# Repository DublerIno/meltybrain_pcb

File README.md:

first iteration of our pcb for melty brain

we are using esp32s3 supermini and high g H3LIS331DL accelerometr. 

to fix:
- vias should not be under the h3 package
- maybe change mounting holes for less mechanical stress of board

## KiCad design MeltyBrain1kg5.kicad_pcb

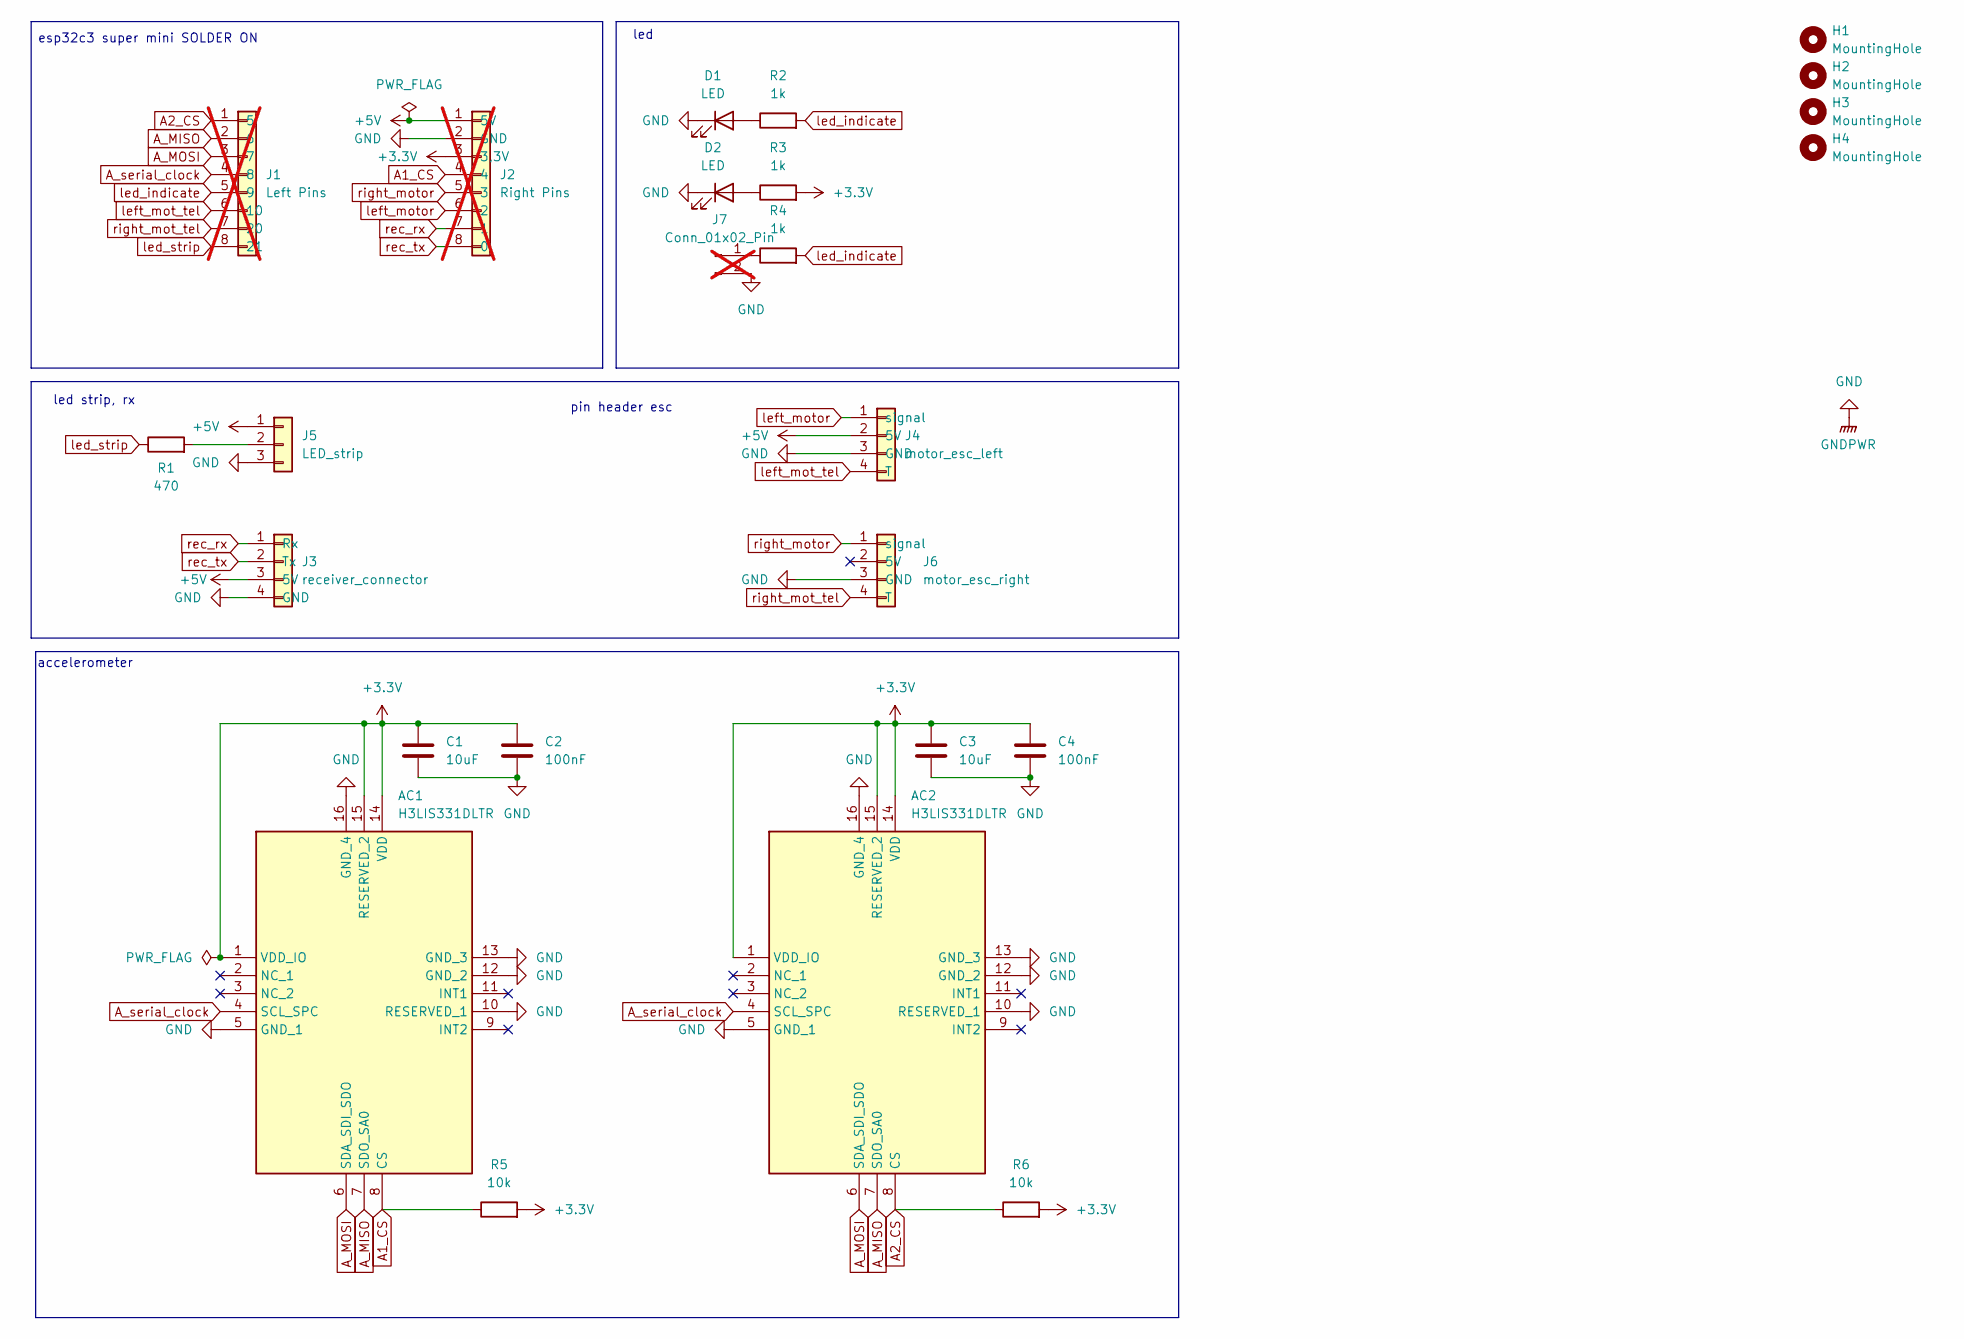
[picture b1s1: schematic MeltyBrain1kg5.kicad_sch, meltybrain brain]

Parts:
AC1, AC2: H3LIS331DLTR; LIS3DHTR; Manufacturer_Part_Number H3LIS331DLTR; Mouser Part Number 511-H3LIS331DLTR
C1, C3: 10uF; C_0603_1608Metric_Pad1.08x0.95mm_HandSolder
C2, C4: 100nF; C_0603_1608Metric_Pad1.08x0.95mm_HandSolder
D1, D2: LED; D_0603_1608Metric_Pad1.05x0.95mm_HandSolder
H1, H2, H3, H4: MountingHole; MountingHole_2.2mm_M2
J1: Left Pins; PinHeader_1x08_P2.54mm_Vertical; not fitted
J2: Right Pins; PinHeader_1x08_P2.54mm_Vertical; not fitted
J3: receiver_connector; JST_SH_BM04B-SRSS-TB_04x1.00mm_Straight
J4: motor_esc_left; PinHeader_1x04_P2.54mm_Vertical
J5: LED_strip; PinHeader_1x03_P2.54mm_Vertical
J6: motor_esc_right; PinHeader_1x04_P2.54mm_Vertical
J7: Conn_01x02_Pin; PinSocket_1x02_P2.54mm_Vertical; not fitted
R1: 470; R_0603_1608Metric_Pad0.98x0.95mm_HandSolder
R2, R3, R4: 1k; R_0603_1608Metric_Pad0.98x0.95mm_HandSolder
R5, R6: 10k; R_0603_1608Metric_Pad0.98x0.95mm_HandSolder

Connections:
+3.3V: AC1.1 (VDD_IO), AC1.14 (VDD), AC1.15 (RESERVED_2), AC2.1 (VDD_IO), AC2.14 (VDD), AC2.15 (RESERVED_2), C1.1, C2.1, C3.1, C4.1, J2.3 (3,3V), R3.2, R5.2, R6.2
+5V: J2.1 (5V), J3.3 (5V), J4.2 (5V), J5.1
A1_CS: AC1.8 (CS), J2.4, R5.1
A2_CS: AC2.8 (CS), J1.1 (5), R6.1
A_MISO: AC1.7 (SDO_SA0), AC2.7 (SDO_SA0), J1.2 (6)
A_MOSI: AC1.6 (SDA_SDI_SDO), AC2.6 (SDA_SDI_SDO), J1.3 (7)
A_serial_clock: AC1.4 (SCL_SPC), AC2.4 (SCL_SPC), J1.4 (8)
GND: AC1.5 (GND_1), AC1.10 (RESERVED_1), AC1.12 (GND_2), AC1.13 (GND_3), AC1.16 (GND_4), AC2.5 (GND_1), AC2.10 (RESERVED_1), AC2.12 (GND_2), AC2.13 (GND_3), AC2.16 (GND_4), C1.2, C2.2, C3.2, C4.2, D1.1 (K), D2.1 (K), J2.2 (GND), J3.4 (GND), J4.3 (GND), J5.3, J6.3 (GND), J7.2
unnamed: D1.2 (A), R2.1
unnamed: D2.2 (A), R3.1
unnamed: J5.2, R1.2
unnamed: J7.1, R4.1
led_indicate: J1.5 (9), R2.2, R4.2
led_strip: J1.8 (21), R1.1
left_mot_tel: J1.6 (10), J4.4 (T)
left_motor: J2.6 (2), J4.1 (signal)
rec_rx: J2.7 (1), J3.1 (Rx)
rec_tx: J2.8 (0), J3.2 (Tx)
right_mot_tel: J1.7 (20), J6.4 (T)
right_motor: J2.5 (3), J6.1 (signal)

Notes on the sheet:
led strip, rx
accelerometer
pin header esc
esp32c3 super mini SOLDER ON
led

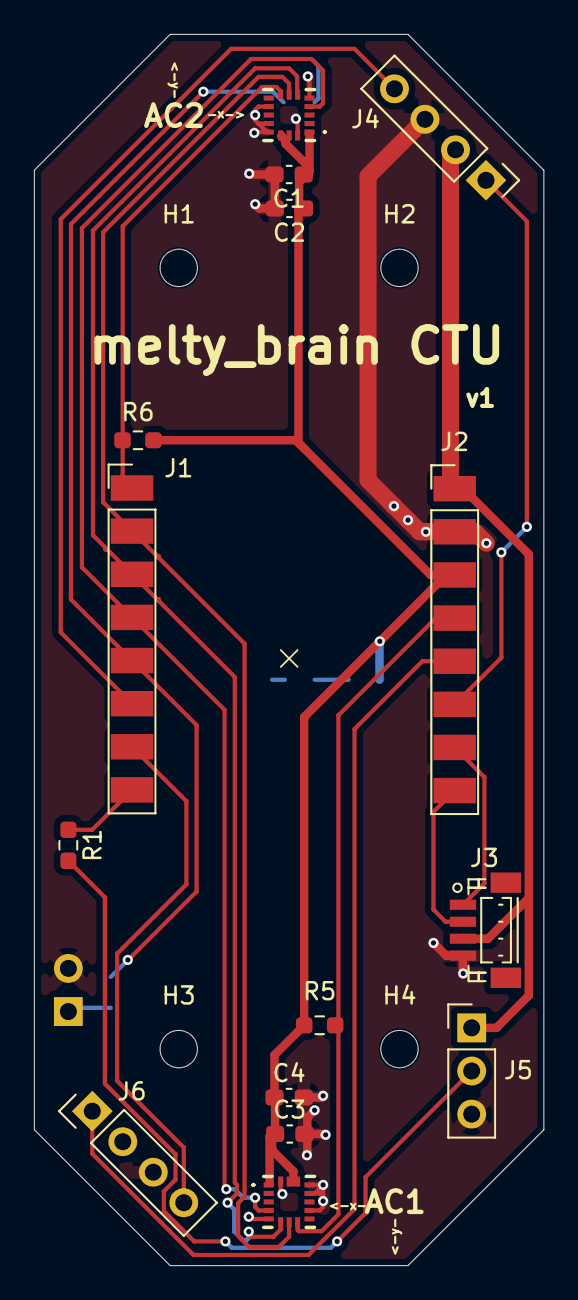
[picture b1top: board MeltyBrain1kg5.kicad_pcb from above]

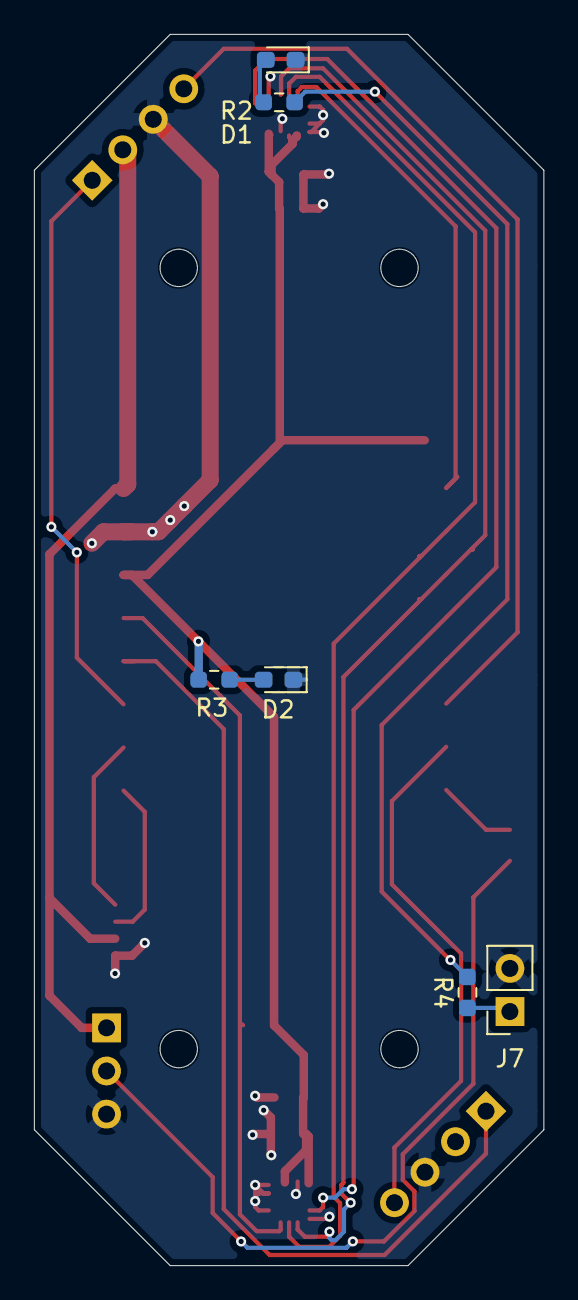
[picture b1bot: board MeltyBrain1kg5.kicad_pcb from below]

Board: 2 copper layers, 30.0 x 72.5 mm, 25 parts (6 on the bottom side), 20 nets.
